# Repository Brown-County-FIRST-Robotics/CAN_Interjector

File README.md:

# CAN Interjector

To panelize, run
```
kikit panelize --layout 'grid; rows: 5; cols: 1; hspace: 1mm; vspace: 1mm;' --cuts 'mousebites' CAN_Interjector.kicad_pcb panelized.kicad_pcb
```

Use [this extension](https://github.com/Bouni/kicad-jlcpcb-tools) to export it

[switch link](https://www.digikey.com/en/products/detail/e-switch/TL2201OAZB/1805524)
[terminal link](https://www.digikey.com/en/products/detail/wago-corporation/2601-1102/17122694)

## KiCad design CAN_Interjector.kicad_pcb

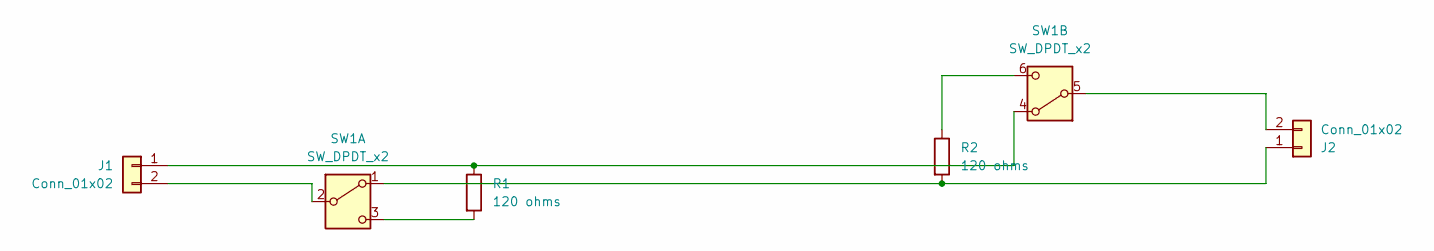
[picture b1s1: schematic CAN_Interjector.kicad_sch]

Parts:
J1, J2: Conn_01x02; TerminalBlock_WAGO_2601-1102_1x02_P3.50mm_Horizontal
R1, R2: 120 ohms; R_0603_1608Metric
SW1: SW_DPDT_x2; SW_TL2201EEYA_EWI

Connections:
unnamed: J1.1, R1.1, SW1.4 (A)
unnamed: J1.2, SW1.2 (B)
unnamed: J2.1, R2.2, SW1.1 (A)
unnamed: J2.2, SW1.5 (B)
unnamed: R1.2, SW1.3 (C)
unnamed: R2.1, SW1.6 (C)

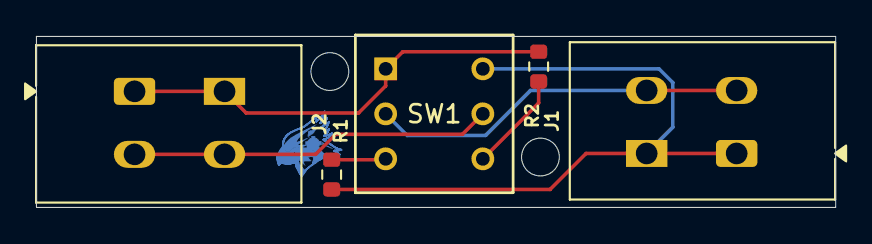
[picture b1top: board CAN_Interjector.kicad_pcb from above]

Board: 2 copper layers, 44.4 x 9.5 mm, 5 parts (0 on the bottom side), 6 nets.

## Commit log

2026-02-28 Add basic elements
2026-02-28 Add project title to README
2026-02-28 Add license
2026-02-28 Cut down board, added traces, added 3d models
2026-02-28 Add redbird logo
2026-03-01 Move the wagos around
2026-03-01 Add LCSC Properties
2026-03-01 Add more notes to readme
2026-03-10 Fix stupid encoders
